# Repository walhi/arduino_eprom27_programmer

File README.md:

# Программатор для EPROM 27 серии (16-512) на Arduino

*Скачивайте архив с вкладки "Releases". Там находится GUI приложение и скетч для arduino*

Список поддерживаемых микросхем (не все микросхемы протестированы):

 * 27C16 (connects from 3 to 26 leg DIP28 socket)
 * 27C32 (connects from 3 to 26 leg DIP28 socket)
 * 27C64
 * 27C128
 * 27C256
 * 27C512

Перед прошивкой уточните напряжение программирования для вашей микросхемы в datasheet'е! 

# Схема
Изначальный проект базировался на проекте: <https://github.com/bouletmarc/BMBurner>
Этот проект является переработанной версией: <https://github.com/walhi/arduino_eprom27_programmer>

Принципиальная схема

Внешний вид

Файлы для производства платы ледат в папке gerber. Исходники проекта доступны тут: <https://oshwlab.com/naym1993/walhi_eeprom_prog>

Список компонентов можно взять в файле 27.pdf
# Software

Управляющая программа взята с оригинального репозитория.

Функции:

 * Чтение чипа
 * Запись чипа
 * Верификация и проверка чипа на запись (no bits to be set to 1)
 * Контроль напряжения программирования (for AVR in TQFP case)

Приложение требует Windows 7 и выше.

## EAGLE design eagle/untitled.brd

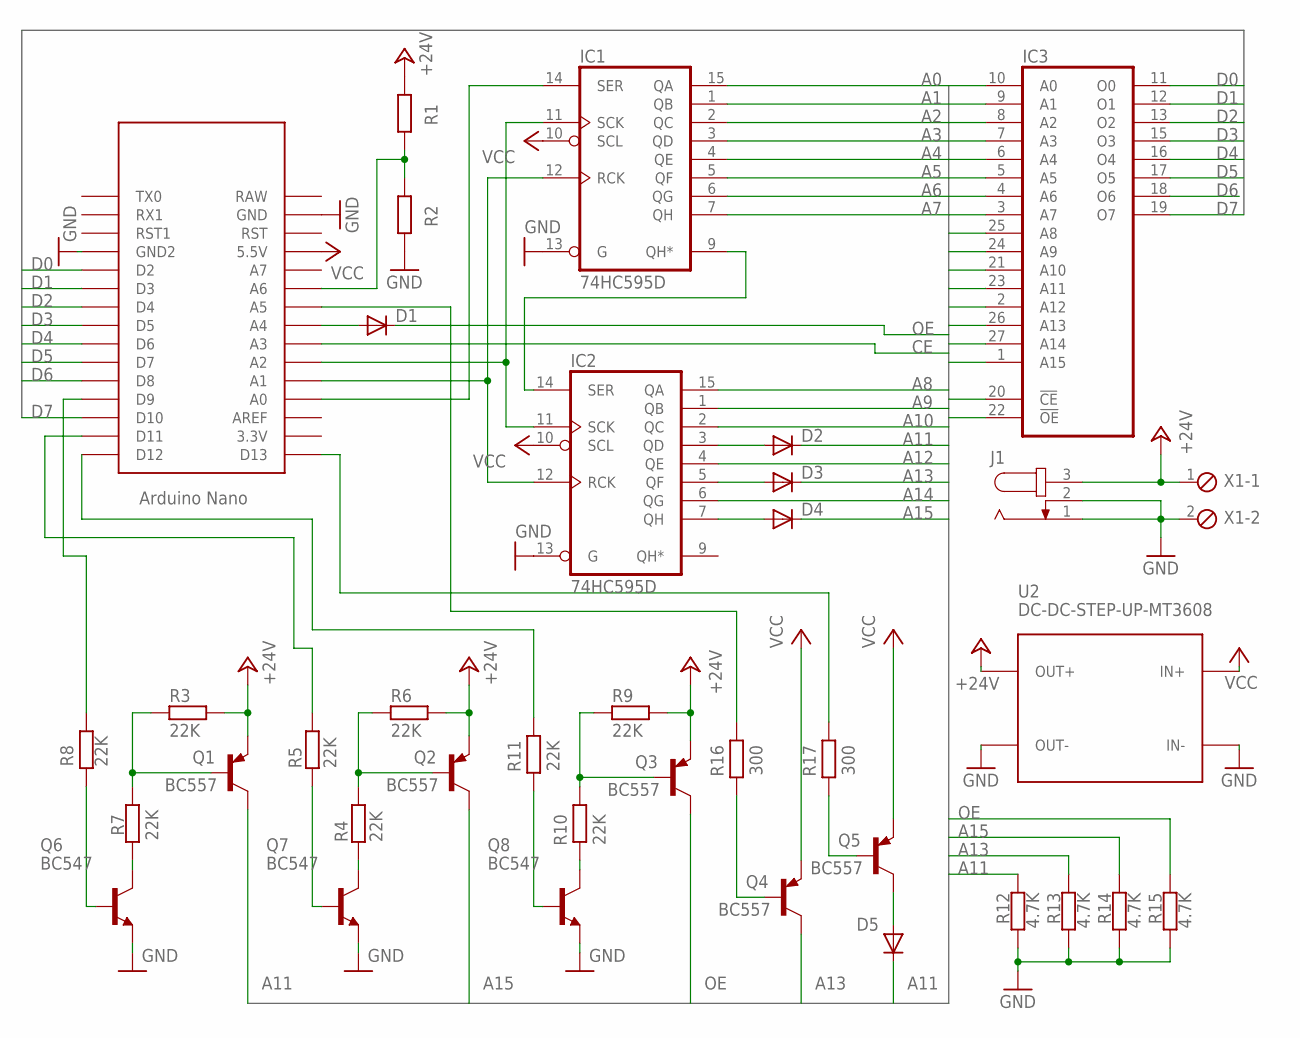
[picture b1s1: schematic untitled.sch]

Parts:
D1, D2, D3, D4, D5: 1N4446; DO35-10
IC1, IC2: 74HC595D; SO16
IC3: 27512; DIL28
J1: JACK-PLUG1; SPC4078
Q1, Q2, Q3, Q4, Q5: BC557; TO92
Q6, Q7, Q8: BC547; TO92
R1, R2: R-EU_M0805; M0805
R3, R4, R5, R6, R7, R8, R9, R10, R11: 22K; M0805
R12, R13, R14, R15: 4.7K; M0805
R16, R17: 300; M0805
U1: NANO
U2: DC-DC-STEP-UP-MT3608
X1: MPT2; 2POL254

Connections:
+24V: J1.3, Q1.1 (E), Q2.1 (E), Q3.1 (E), R1.1, R3.2, R6.2, R9.2, U2.OUT+, X1.1
A0: IC1.15 (QA), IC3.10 (A0)
A1: IC1.1 (QB), IC3.9 (A1)
A2: IC1.2 (QC), IC3.8 (A2)
A3: IC1.3 (QD), IC3.7 (A3)
A4: IC1.4 (QE), IC3.6 (A4)
A5: IC1.5 (QF), IC3.5 (A5)
A6: IC1.6 (QG), IC3.4 (A6)
A7: IC1.7 (QH), IC3.3 (A7)
A8: IC2.15 (QA), IC3.25 (A8)
A9: IC2.1 (QB), IC3.24 (A9)
A10: IC2.2 (QC), IC3.21 (A10)
A11: D2.C, D5.C, IC3.23 (A11), Q1.3 (C), R12.1
A12: IC2.4 (QE), IC3.2 (A12)
A13: D3.C, IC3.26 (A13), Q4.3 (C), R13.1
A14: IC2.6 (QG), IC3.27 (A14)
A15: D4.C, IC3.1 (A15), Q2.3 (C), R14.1
CE: IC3.20 (!CE), U1.A3
D0: IC3.11 (O0), U1.D2
D1: IC3.12 (O1), U1.D3
D2: IC3.13 (O2), U1.D4
D3: IC3.15 (O3), U1.D5
D4: IC3.16 (O4), U1.D6
D5: IC3.17 (O5), U1.D7
D6: IC3.18 (O6), U1.D8
D7: IC3.19 (O7), U1.D10
GND: IC1.8 (GND), IC1.13 (G), IC2.8 (GND), IC2.13 (G), IC3.14 (GND), J1.1, J1.2, Q6.1 (E), Q7.1 (E), Q8.1 (E), R2.2, R12.2, R13.2, R14.2, R15.2, U1.GND, U1.GND1 (GND2), U2.IN-, U2.OUT-, X1.2
unnamed: IC1.11 (SCK), IC2.11 (SCK), U1.A2
unnamed: IC1.12 (RCK), IC2.12 (RCK), U1.A1
unnamed: IC1.9 (QH*), IC2.14 (SER)
unnamed: IC1.14 (SER), U1.A0
unnamed: D2.A, IC2.3 (QD)
unnamed: D3.A, IC2.5 (QF)
unnamed: R8.1, U1.D9
unnamed: D1.A, U1.A4
unnamed: R1.2, R2.1, U1.A6
unnamed: R16.1, U1.A5
unnamed: R5.2, U1.D11
unnamed: R17.1, U1.D13
unnamed: R11.1, U1.D12
unnamed: D4.A, IC2.7 (QH)
unnamed: D5.A, Q5.3 (C)
unnamed: Q8.3 (C), R10.2
unnamed: Q3.2 (B), R9.1, R10.1
unnamed: Q8.2 (B), R11.2
unnamed: Q7.3 (C), R4.1
unnamed: Q2.2 (B), R4.2, R6.1
unnamed: Q7.2 (B), R5.1
unnamed: Q6.3 (C), R7.2
unnamed: Q1.2 (B), R3.1, R7.1
unnamed: Q6.2 (B), R8.2
unnamed: Q4.2 (B), R16.2
unnamed: Q5.2 (B), R17.2
OE: D1.C, IC3.22 (!OE), Q3.3 (C), R15.1
VCC: IC1.10 (SCL), IC1.16 (VCC), IC2.10 (SCL), IC2.16 (VCC), IC3.28 (VCC), Q4.1 (E), Q5.1 (E), U1.5V (5.5V), U2.IN+

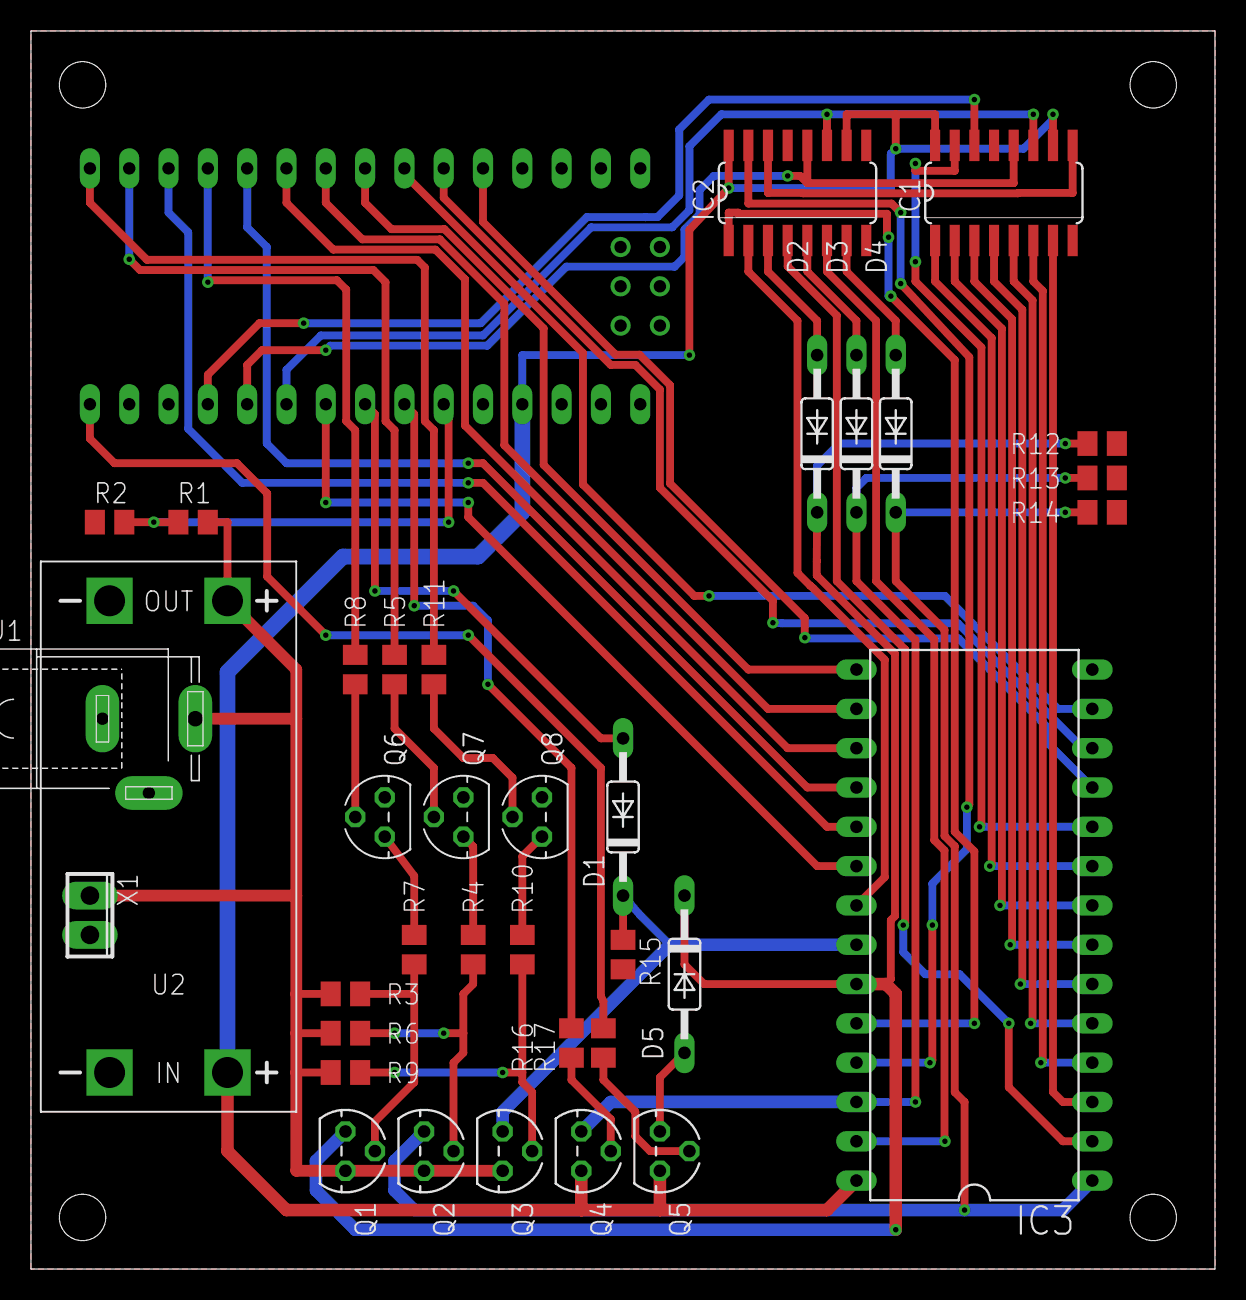
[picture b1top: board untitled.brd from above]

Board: 2 copper layers, 76.5 x 80.0 mm, 37 parts (0 on the bottom side), 55 nets.

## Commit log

2019-03-10 Import code from local repository.
2019-07-24 Исправления схемы.
2019-12-21 Checkpoint. Начало переноса кода работы с ардуинёй в отдельный класс. Вроде бы работает чтение. Остальное как нибудь потом...
2020-04-04 Fix typo in verify subroutine.
2021-04-30 изменен sketch и описание репозитория. Добавлены gerber
2021-04-30 поправлен readme
2021-06-26 работу с hc595 перевел на spi, изменен опорный источник для ацп
2021-06-30 добвлен pdf с описанием, обновлена схема
2023-03-08 Fix typo QT6 update

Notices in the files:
parts and their libraries:
diy-modules: Released under the Creative Commons Attribution 4.0 International License: http://creativecommons.org/licenses/by/4.0
